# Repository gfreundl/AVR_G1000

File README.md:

G1000 HID unit 

This is a hardware simulator for the G1000, the most popular glass cockpit system in the GA fleet.  

The 3D model is based on the original device, has accurate dimensions and is available in STP format.  

Schematics and PCB layout are in the Eagle folder.  
All inputs are read by three ATMega16 MCU with USB firmware, linked together on a FE1.1s USB Hub chip.
No BOM is provided, as most parts are generic. The encoders are Alps STEC (volume) and ELMA E33 / E37 (all others)
The joystick is an Alps RKJXT1F42001, which is soldered on the copper side.

Sourcecode is mainly based on the V-USB driver firmware from obdev/v-usb

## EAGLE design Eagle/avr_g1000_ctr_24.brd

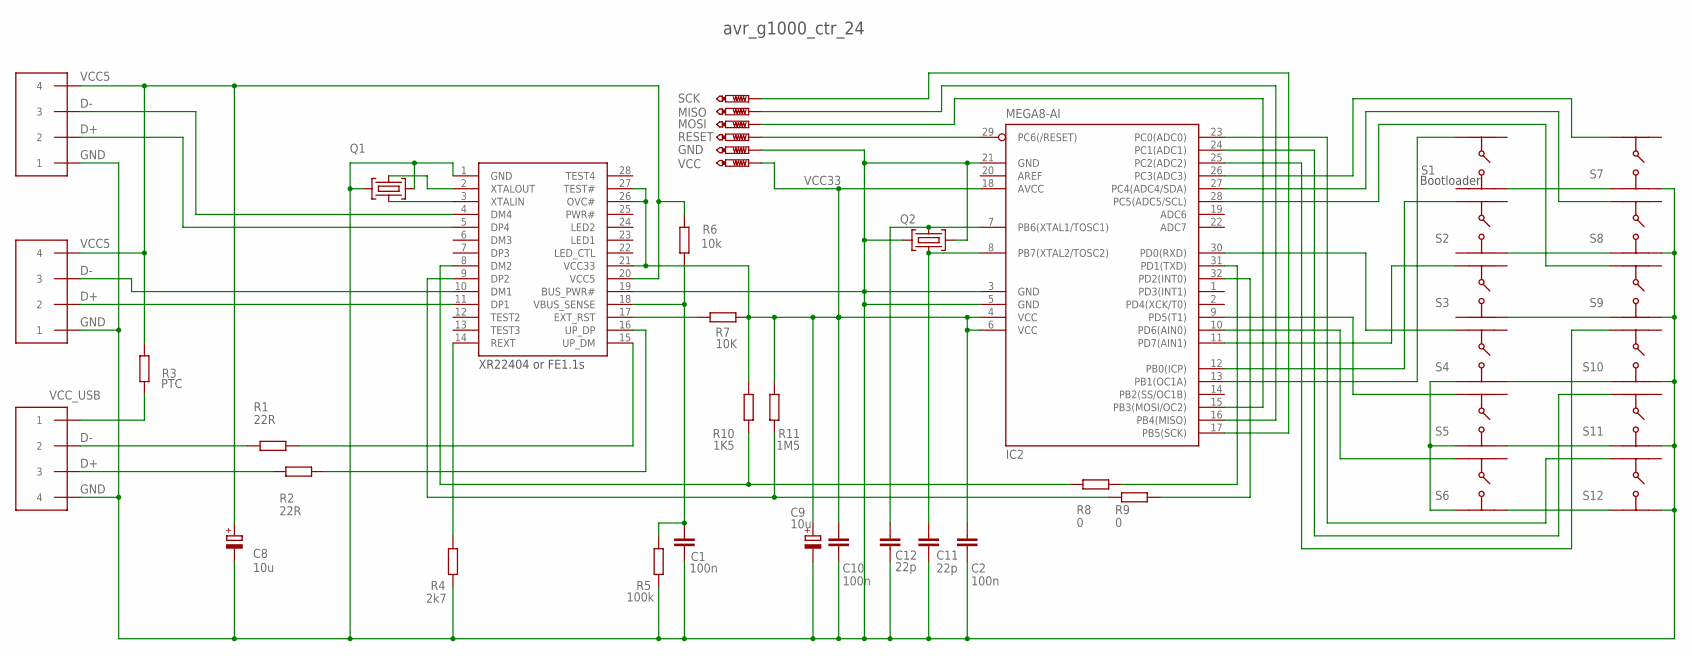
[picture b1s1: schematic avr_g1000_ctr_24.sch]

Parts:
C1, C2, C10: 100n; C0402
C8, C9: 10u; SMC_A
C11, C12: 22p; C0402
GND: PTR1TP10R; TP10R
IC2: MEGA8-AI; TQFP32-08
MISO: PTR1TP10R; TP10R
MOSI: PTR1TP10R; TP10R
Q1: 12MHz; OSCCC500X320X100
Q2: 12Mhz; OSCCC500X320X100
R1, R2: 22R; R0603
R3: PTC; R0805
R4: 2k7; R0603
R5: 100k; R0603
R6: 10k; R0603
R7: 10K; R0603
R8, R9: 0; R0603
R10: 1K5; R0603
R11: 1M5; R0603
RESET: PTR1TP10R; TP10R
S1, S2, S3, S4, S5, S6, S7, S8, S9, S10, S11, S12: B3FS1000
SCK: PTR1TP10R; TP10R
U$1, U$2, U$3: HEADER4X1.27
VCC: PTR1TP10R; TP10R
XR22404: XR22404

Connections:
D+: R2.1, U$1.P3 (3)
D-: R1.1, U$1.P2 (2)
DM1: U$2.P3 (3), XR22404.10 (DM1)
DM2: R8.1, R10.1, XR22404.8 (DM2)
DM4: U$3.P3 (3), XR22404.4 (DM4)
DP1: U$2.P2 (2), XR22404.11 (DP1)
DP2: R9.1, R11.1, XR22404.9 (DP2)
DP4: U$3.P2 (2), XR22404.5 (DP4)
EXT_RST: R7.1, XR22404.17 (EXT_RST)
GND: C1.2, C2.2, C8.-, C9.-, C10.2, C11.2, C12.2, GND.TP, IC2.3 (GND), IC2.5 (GND), IC2.21 (GND), Q1.2 (GND1), Q1.4 (GND2), Q2.2 (GND1), Q2.4 (GND2), R4.1, R5.1, S1.1, S2.1, S3.1, S4.1, S4.2, S5.1, S5.2, S6.1, S6.2, S7.1, S7.2, S8.1, S8.2, S9.1, S9.2, S10.1, S10.2, S11.1, S11.2, S12.1, S12.2, U$1.P4 (4), U$2.P1 (1), U$3.P1 (1), XR22404.1 (GND), XR22404.19 (BUS_PWR#)
MISO: IC2.16 (PB4(MISO)), MISO.TP
MOSI: IC2.15 (PB3(MOSI/OC2)), MOSI.TP
PB0: IC2.12 (PB0(ICP)), S2.4
PB1: IC2.13 (PB1(OC1A)), S1.4
PC0: IC2.23 (PC0(ADC0)), S12.4
PC1: IC2.24 (PC1(ADC1)), S11.4
PC2: IC2.25 (PC2(ADC2)), S10.4
PC3: IC2.26 (PC3(ADC3)), S7.4
PC4: IC2.27 (PC4(ADC4/SDA)), S8.4
PC5: IC2.28 (PC5(ADC5/SCL)), S9.4
PD0: IC2.30 (PD0(RXD)), S4.4
PD1: IC2.31 (PD1(TXD)), R8.2
PD2: IC2.32 (PD2(INT0)), R9.2
PD5: IC2.9 (PD5(T1)), S5.4
PD6: IC2.10 (PD6(AIN0)), S6.4
PD7: IC2.11 (PD7(AIN1)), S3.4
RESET: IC2.29 (PC6(/RESET)), RESET.TP
REXT: R4.2, XR22404.14 (REXT)
SCK: IC2.17 (PB5(SCK)), SCK.TP
UP_DM: R1.2, XR22404.15 (UP_DM)
UP_DP: R2.2, XR22404.16 (UP_DP)
VBUS_SENSE: C1.1, R5.2, R6.1, XR22404.18 (VBUS_SENSE)
VCC5: C8.+, R3.2, R6.2, U$2.P4 (4), U$3.P4 (4), XR22404.20 (VCC5)
VCC33: C2.1, C9.+, C10.1, IC2.4 (VCC), IC2.6 (VCC), IC2.18 (AVCC), R7.2, R10.2, R11.2, VCC.TP, XR22404.21 (VCC33), XR22404.26 (OVC#), XR22404.27 (TEST#)
VCC_USB: R3.1, U$1.P1 (1)
XTAL1: C12.1, IC2.7 (PB6(XTAL1/TOSC1)), Q2.1 (CRYSTAL1)
XTAL2: C11.1, IC2.8 (PB7(XTAL2/TOSC2)), Q2.3 (CRYSTAL2)
XTALIN: Q1.3 (CRYSTAL2), XR22404.3 (XTALIN)
XTALOUT: Q1.1 (CRYSTAL1), XR22404.2 (XTALOUT)

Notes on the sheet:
avr_g1000_ctr_24
XR22404 or FE1.1s
Bootloader

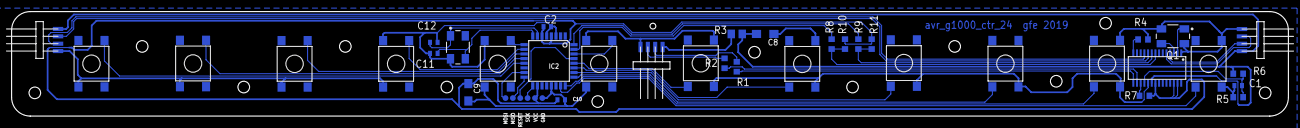
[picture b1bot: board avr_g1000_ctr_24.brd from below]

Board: 2 copper layers, 220.0 x 18.0 mm, 43 parts (43 on the bottom side), 39 nets.

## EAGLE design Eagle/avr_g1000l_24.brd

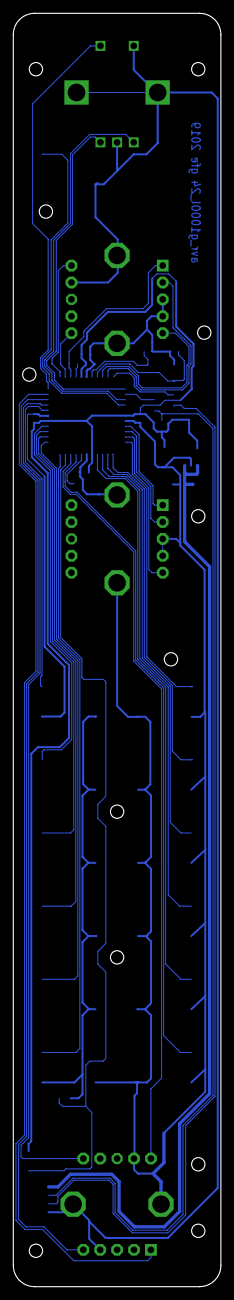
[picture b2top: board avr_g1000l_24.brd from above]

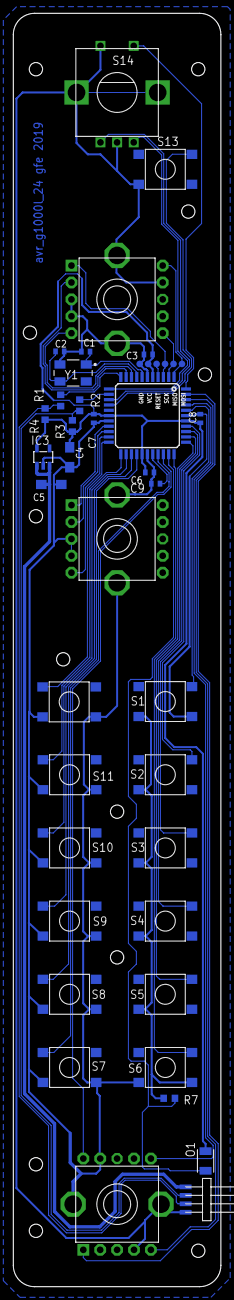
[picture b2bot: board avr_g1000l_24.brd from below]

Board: 2 copper layers, 31.2 x 191.4 mm, 42 parts (42 on the bottom side), 40 nets.

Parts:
C1, C2, C3, C6, C7, C8, C9: C0402
C4, C5: SMC_A
GND: TPTP10R; TP10R
IC1: MEGA16-A; TQFP44
IC3: LP2981M5; SOT23-5
MISO: TPTP10R; TP10R
MOSI: TPTP10R; TP10R
O1: KPS-3227KPS-3227; RESC3216X110
R1, R2, R7: R0603
R3: 1K5; R0603
R4: 1M5; R0603
RESET: TPTP10R; TP10R
S1, S2, S3, S4, S5, S6, S7, S8, S9, S10, S11, S12, S13: B3FS1000
S14: ALPS_EC12ALPS_EC12; ALPS_EC12E_SW
S16, S17, S18: ELMA_E37
SCK: TPTP10R; TP10R
U$4: HEADER4X1.27
VCC: TPTP10R; TP10R
Y1: MJ-CRYSTALMJ; OSCCC500X320X100

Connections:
D+: R2.2, R3.1, U$4.P2
D-: R1.1, R4.1, U$4.P3
GND: C1.2, C2.2, C3.2, C4.-, C5.-, C6.2, C7.2, C8.2, C9.2, GND.TP, IC1.6, IC1.18, IC1.28, IC1.39, IC3.2, R7.1, S1.3, S1.4, S2.3, S2.4, S3.3, S3.4, S4.3, S4.4, S5.3, S5.4, S6.3, S6.4, S7.3, S7.4, S8.3, S8.4, S9.3, S9.4, S10.3, S10.4, S11.3, S11.4, S12.3, S12.4, S13.3, S13.4, S14.C, S14.D, S14.GND1, S14.GND2, S16.P3, S16.P4, S16.P9, S16.P11, S16.P12, S17.P3, S17.P4, S17.P11, S17.P12, S18.P4, S18.P9, S18.P11, S18.P12, U$4.P4, Y1.2
PA0: IC1.37, S2.2
PA1: IC1.36, S3.2
PA2: IC1.35, S4.2
PA3: IC1.34, S5.2
PA4: IC1.33, S6.2
PA5: IC1.32, O1.2, R7.2
PA6: IC1.31, S18.P10
PA7: IC1.30, S7.1
PB0: IC1.40, S1.2
PB1: IC1.41, S18.P6
PB2: IC1.42, S18.P5
PB3: IC1.43, S18.P1
PB4: IC1.44, S14.E
PB5: IC1.3, S16.P1, SCK.TP
PB6: IC1.1, MOSI.TP, S16.P10
PB7: IC1.2, MISO.TP, S16.P6
PC0: IC1.19, S17.P1
PC1: IC1.20, S17.P2
PC2: IC1.21, S17.P5
PC3: IC1.22, S12.1
PC4: IC1.23, S11.1
PC5: IC1.24, S10.1
PC6: IC1.25, S9.1
PC7: IC1.26, S8.1
PD0: IC1.9, S16.P5
PD1: IC1.10, S16.P2
PD2: IC1.13, R2.1
PD3: IC1.12, S14.B
PD4: IC1.11, R1.2
PD5: IC1.14, S14.A
PD6: IC1.15, S13.2
RESET: IC1.4, RESET.TP
V5V: C5.+, IC3.1, IC3.3, U$4.P1
VCC: C3.1, C4.+, C6.1, C7.1, C8.1, IC1.5, IC1.17, IC1.27, IC1.38, IC3.5, O1.1, R3.2, R4.2, VCC.TP
VREF: C9.1, IC1.29
XTAL1: C2.1, IC1.8, Y1.3
XTAL2: C1.1, IC1.7, Y1.1

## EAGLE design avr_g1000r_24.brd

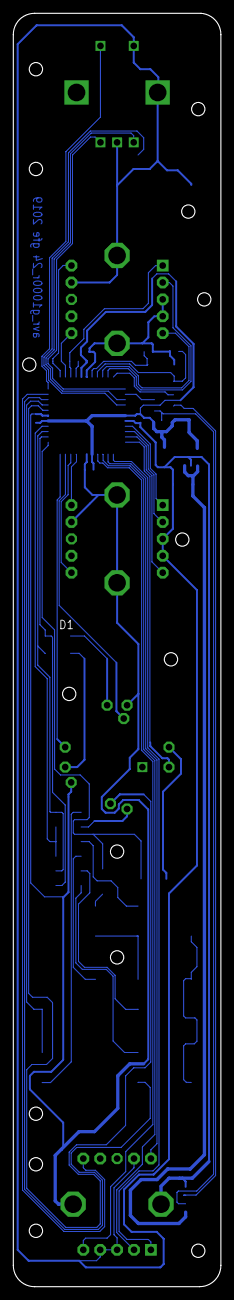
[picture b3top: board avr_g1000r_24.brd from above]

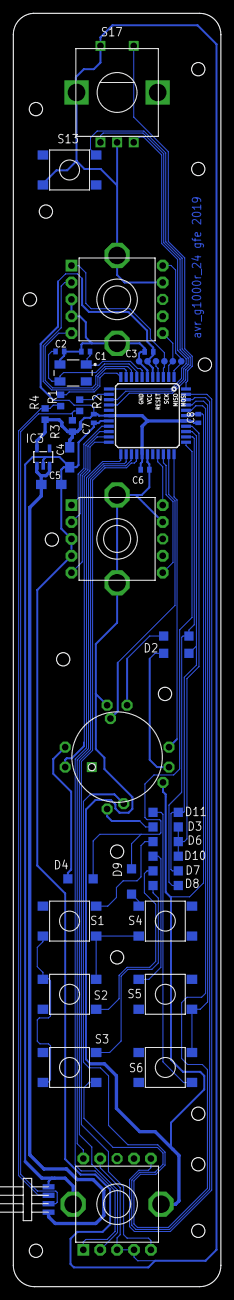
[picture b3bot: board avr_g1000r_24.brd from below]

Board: 2 copper layers, 31.2 x 191.4 mm, 44 parts (44 on the bottom side), 49 nets.

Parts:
C1, C2, C3, C6, C7, C8: C0402
C4, C5: 10u; SMC_A
D1, D2, D3, D4, D6, D7, D8, D9, D10, D11: SOD123
GND: PTR1TP10R; TP10R
IC1: MEGA16-A; TQFP44
IC3: LP2981M5; SOT23-5
MISO: PTR1TP10R; TP10R
MOSI: PTR1TP10R; TP10R
R1, R2: R0603
R3: 1K5; R0603
R4: 1M5; R0603
RESET: PTR1TP10R; TP10R
S1, S2, S3, S4, S5, S6: B3FS1000
S7: RKJXT1F42001
S13: Bootloader; B3FS1000
S14, S15, S16: ELMA_E37
S17: ALPS_EC12ALPS_EC12; ALPS_EC12E_SW
SCK: PTR1TP10R; TP10R
U$4: HEADER4X1.27
VCC: PTR1TP10R; TP10R
Y1: 12MHz; OSCCC500X320X100

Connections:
D1: D1.C, S7.C
D2: D2.C, S7.B
D3: D3.C, S7.A
D4: D4.C, S7.D
D7: D7.C, S2.1
D8: D8.C, S3.2
D10: D10.C, S5.1
D11: D11.C, S6.1
D+: R1.1, R4.1, U$4.P3
D-: R2.2, R3.1, U$4.P2
GND: C1.2, C2.2, C3.2, C4.-, C5.-, C6.2, C7.2, C8.2, GND.TP, IC1.6, IC1.18, IC1.28, IC1.39, IC3.2, S7.ENC_COM, S7.GND, S13.3, S14.P3, S14.P4, S14.P9, S14.P11, S14.P12, S15.P3, S15.P4, S15.P9, S15.P11, S15.P12, S16.P3, S16.P4, S16.P9, S16.P11, S16.P12, S17.C, S17.D, S17.GND1, S17.GND2, U$4.P4, Y1.2
unnamed: D9.C, S4.1
unnamed: IC1.21, S15.P5
unnamed: D6.C, S1.2
PA0: D3.A, D6.A, D10.A, IC1.37
PA1: D2.A, D7.A, D11.A, IC1.36
PA2: D1.A, D8.A, IC1.35
PA3: D4.A, D9.A, IC1.34
PA4: IC1.33, S7.ENC_B
PA5: IC1.32, S7.COM
PA6: IC1.31, S15.P6
PA7: IC1.30, S15.P10
PB0: IC1.40, S7.PUSH
PB1: IC1.41, S5.4, S6.3
PB2: IC1.42, S1.3, S1.4, S2.3, S2.4, S3.3, S3.4, S4.3
PB3: IC1.43, S16.P6
PB4: IC1.44, S17.E
PB5: IC1.1, MOSI.TP, S14.P10
PB6: IC1.2, MISO.TP, S14.P6
PB7: IC1.3, S14.P1, SCK.TP
PC0: IC1.19, S15.P1
PC1: IC1.20, S15.P2
PC3: IC1.22, S7.ENC_A
PC4: IC1.23, S16.P1
PC5: IC1.24, S16.P10
PC6: IC1.25, S16.P2
PC7: IC1.26, S16.P5
PD0: IC1.9, S14.P5
PD1: IC1.10, S14.P2
PD2: IC1.11, R1.2
PD3: IC1.12, S17.B
PD4: IC1.13, R2.1
PD5: IC1.14, S17.A
PD6: IC1.15, S13.2
RESET: IC1.4, RESET.TP
V5V: C5.+, IC3.1, IC3.3, U$4.P1
VCC: C3.1, C4.+, C6.1, C7.1, C8.1, IC1.5, IC1.17, IC1.27, IC1.38, IC3.5, R3.2, R4.2, VCC.TP
XTAL1: C2.1, IC1.8, Y1.3
XTAL2: C1.1, IC1.7, Y1.1

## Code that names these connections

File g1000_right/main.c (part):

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		PORTA |= 0b11111111;							//pull-up resistors
		PORTB |= 0b11111111;
		PORTC |= 0b11111111;
		PORTD |= 0b11101011;							//no pull-ups on USB ports PD2, PD4

		enc[0] = (enc[0] & 0b00001100) 
					| ((PINA & (1<<PINA4))>>3)			//Alps Encoder RKJX
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
		//Process Analog Inputs
		//customize i for number of potentiometers									// <----- change here
		n = 0;											//ADC5 = PA5
		while (n < 0)
		{
			ReadAnalog();
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}//end ReadButton(void)

//general key matrix
//PB0-2 column output
//PA0-3 row input, PA5 special pin 'Com' on RKJX switch
void ButtonMatrix()
{
	uchar i = 0;
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
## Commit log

2019-08-15 Initial local add and commit
2019-08-15 remove MSB in report byte 4 fix S7 S8

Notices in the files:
g1000_right/main.c:
Copyright: (c) 2008 by OBJECTIVE DEVELOPMENT Software GmbH
License: GNU GPL v2 (see License.txt), GNU GPL v3 or proprietary (CommercialLicense.txt)
